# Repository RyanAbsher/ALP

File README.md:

# ALP

A wireless control system for a balloon-based aerial cave photography lighting platform.

## Introduction
A friend of mine has for a long time wanted to photograph the top of a particular cave chamber that has never been photographed before. The chamber is 396 feet tall, so access to the top is obviously somewhat limited. In the past they have used a 6' diameter weather balloon to lift lighting to the top, then used telephoto lenses to photograph it from the ground. This time they are putting the cameras on the balloon, but they didn't have a good way to control the equipment from the ground. This project is the solution to that problem.

## Hardware
The board is based on an STM32 microcontroller. There are three different boards needed for this project: 1 on the ballon, and 2 in control boxes on the ground. I have designed this PCB so that the same design can be used for all of the locations. It is also generic enough that it can be adapted if this particular project changes, or if we want to use it for other projects in the future. There are 8 dedicated relay outputs (5A DC Max) and 16 general IO connectors. These can be used as inputs or outputs, and each bank of 4 connectors has a jumper that can be used to select either 5v or 3.3v outputs. Each of these 16 outputs can also optionally be used as a servo output, with a dedicated servo driver IC on-board.

Communication between boards is accomplished using USART. The two control boxes are connected with a cable. The balloon-mounted board uses HC-12 serial radio modules to communicate with the primary control box on the ground. In ground-based tests of these radios we have achieved effective communication over distances greater than 1400 meters. I do not anticipate any problem using them to communicated over ~120 meters.

Users on the ground can use the two control boxes to control various equipment on the balloon. There is a DSLR camera mounted on the balloon, and the ISO, Aperture, and Shutter speed can be set from the ground. The shutter can of course also be triggered from the ground. The DSLR is mounted on a custom pan/tilt servo gimbal, and this is fully controllable from the ground.

There are 3 powerful LED lights mounted on the balloon, these are controlled through some of the relay outputs, and their direction can be controlled with a servo attached to each.

There are various other pieces of hardware that are controllable from the ground, although the configuration and type of such is likely to change as the project continues.

## Prototype

The photo above contains the laser-etched acrylic control panels, and the stripboard working prototype that I built. While it admittedly doesn't look that great, it did serve it's purpose in that it showed all of the pieces of the system could communicate and function as expected.

## To Do
I have an STM32 dev board on the way that has the same chip that I will be using on this board (STM32F103RBT6). I will use it to confirm that it can do everything I expect of it, then I will be ordering the PCBs. I will likely be ordering them from JLCPCB, and will have them assemble the SMT components on at least a few of the boards. The boards will be populated differently depending on which location they are currently in. For example, the control boxes will not need the relays populated. I will hand-solder the relays and connectors as needed.

Once I have the boards in hand, then I can write the necessary software. I programmed the protoype using the Arduino environment, and I was happy with the way the software worked. Since I have the software mostly completed, it should be fairly simple to port it over to the STM32, likely using STs STM32CubeIDE software. When the software is complete, I will add it to this repository.

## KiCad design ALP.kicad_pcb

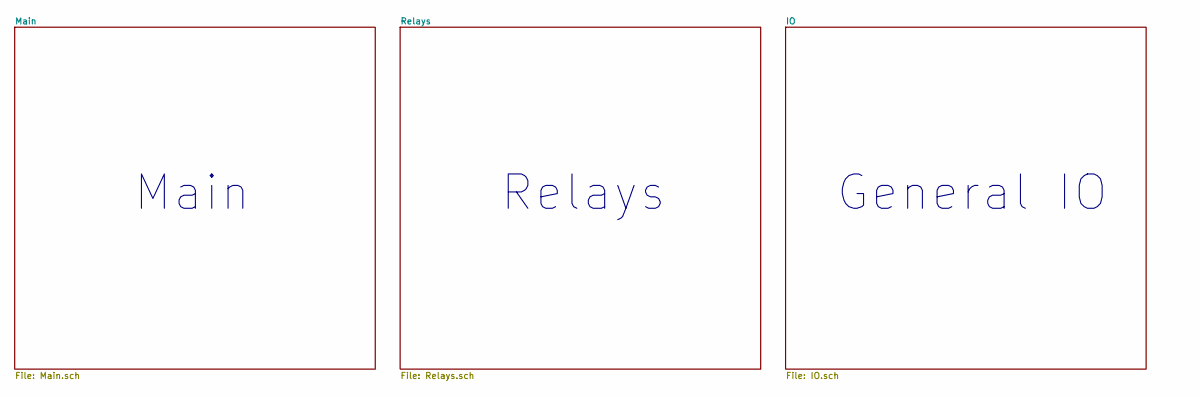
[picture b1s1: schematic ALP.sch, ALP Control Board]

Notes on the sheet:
General IO
Main
Relays

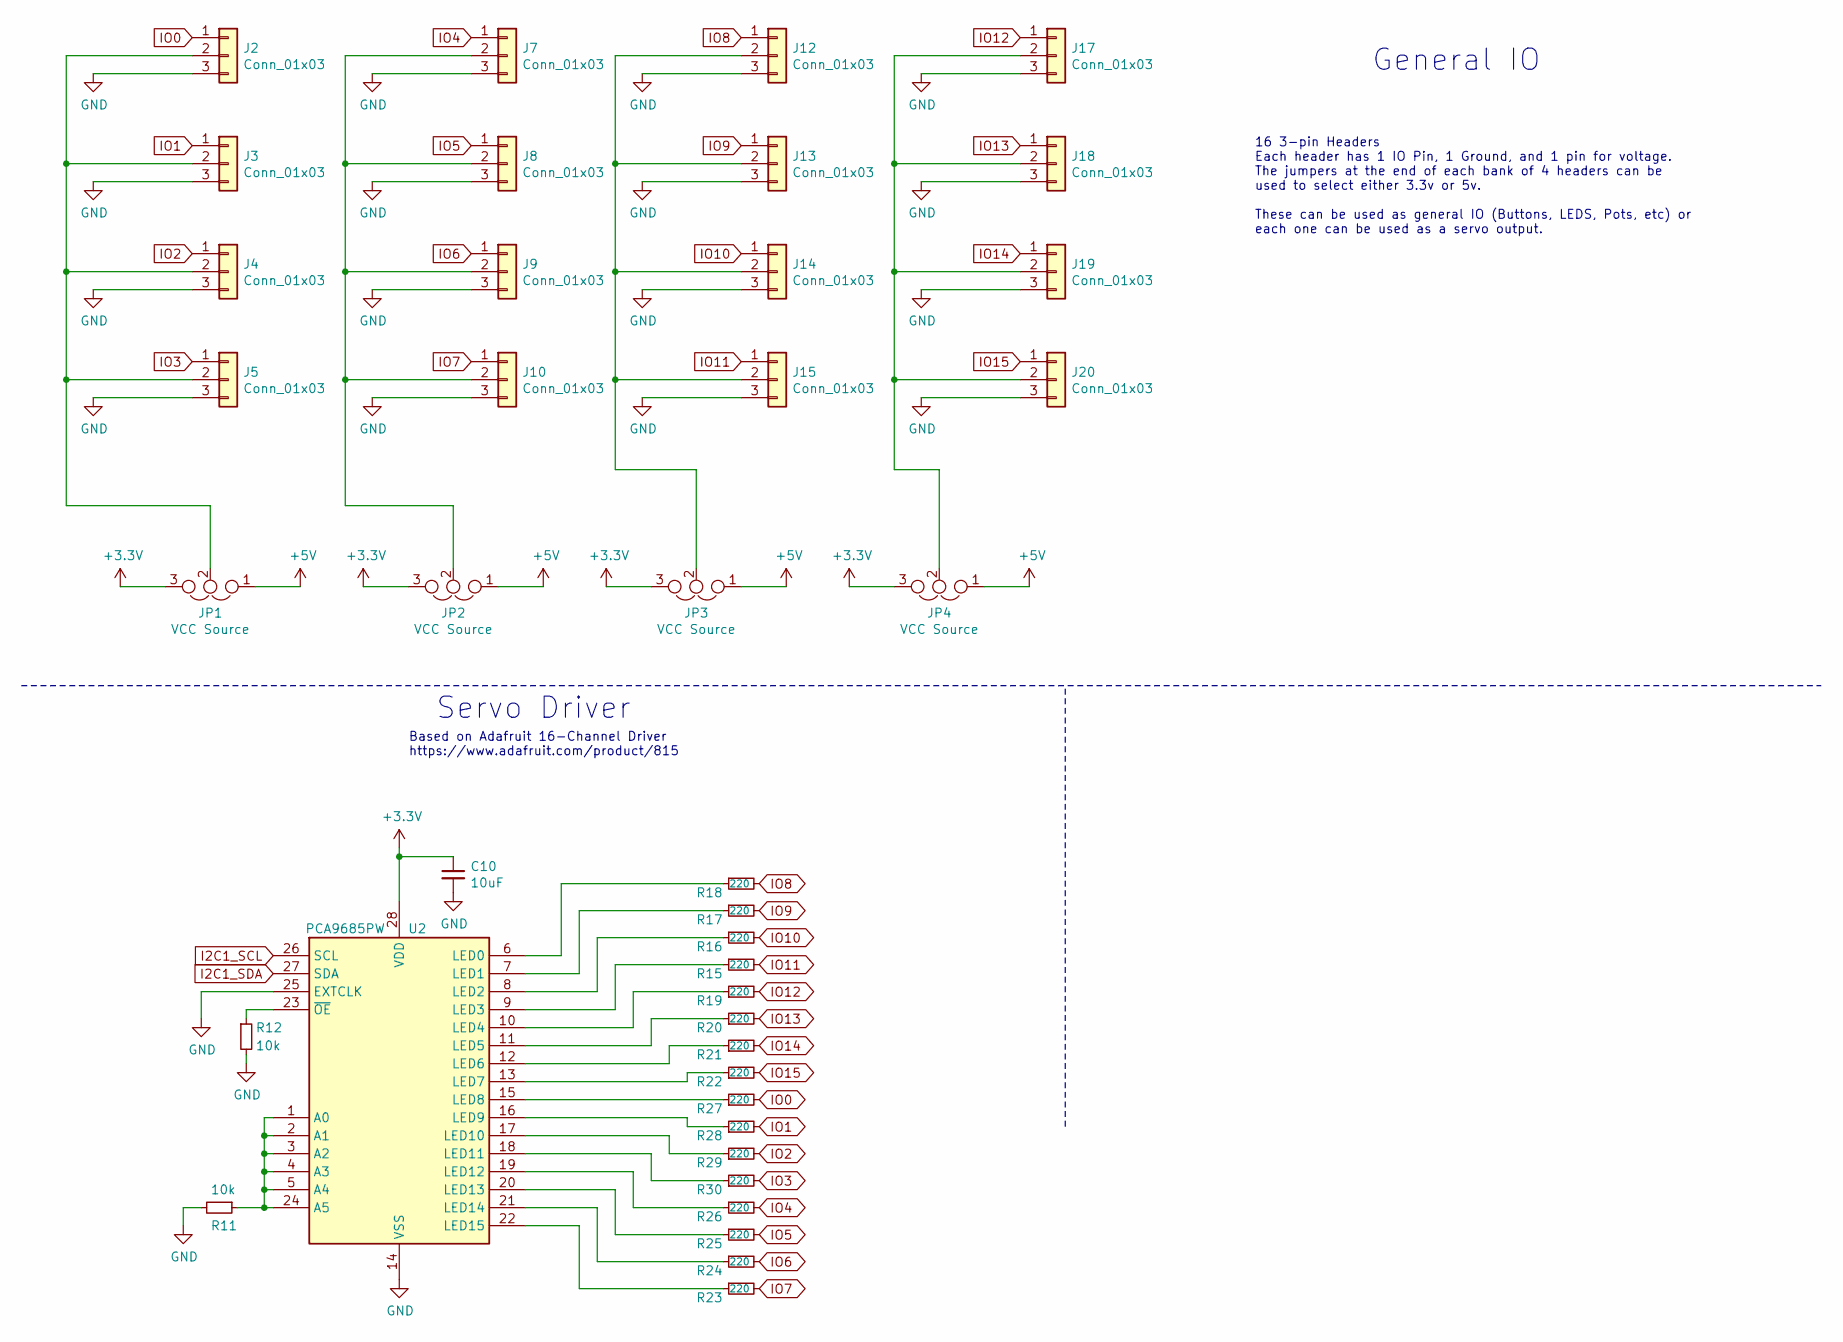
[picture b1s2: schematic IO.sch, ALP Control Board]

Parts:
C10: 10uF; C_0402_1005Metric
J2, J3, J4, J5, J7, J8, J9, J10, J12, J13, J14, J15, J17, J18, J19, J20: Conn_01x03; Molex_PicoBlade_53047-0610_1x03_P1.25mm_Vertical
JP1, JP2, JP3, JP4: VCC Source; PinHeader_1x03_P2.54mm_Vertical
R11, R12: 10k; R_0402_1005Metric
R15, R16, R17, R18, R19, R20, R21, R22, R23, R24, R25, R26, R27, R28, R29, R30: 220; R_0402_1005Metric
U2: PCA9685PW; TSSOP-28_4.4x9.7mm_P0.65mm

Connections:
+3V3: C10.1, JP1.3, JP2.3, JP3.3, JP4.3, U2.28 (VDD); also elsewhere on the board
+5V: JP1.1, JP2.1, JP3.1, JP4.1; also elsewhere on the board
GND: C10.2, J2.3, J3.3, J4.3, J5.3, J7.3, J8.3, J9.3, J10.3, J12.3, J13.3, J14.3, J15.3, J17.3, J18.3, J19.3, J20.3, R11.2, R12.2, U2.14 (VSS), U2.25 (EXTCLK); also elsewhere on the board
I2C1_SCL: U2.26 (SCL); also elsewhere on the board
I2C1_SDA: U2.27 (SDA); also elsewhere on the board
IO0: J2.1, R27.2; also elsewhere on the board
IO1: J3.1, R28.2; also elsewhere on the board
IO2: J4.1, R29.2; also elsewhere on the board
IO3: J5.1, R30.2; also elsewhere on the board
IO4: J7.1, R26.2; also elsewhere on the board
IO5: J8.1, R25.2; also elsewhere on the board
IO6: J9.1, R24.2; also elsewhere on the board
IO7: J10.1, R23.2; also elsewhere on the board
IO8: J12.1, R18.2; also elsewhere on the board
IO9: J13.1, R17.2; also elsewhere on the board
IO10: J14.1, R16.2; also elsewhere on the board
IO11: J15.1, R15.2; also elsewhere on the board
IO12: J17.1, R19.2; also elsewhere on the board
IO13: J18.1, R20.2; also elsewhere on the board
IO14: J19.1, R21.2; also elsewhere on the board
IO15: J20.1, R22.2; also elsewhere on the board
unnamed: J2.2, J3.2, J4.2, J5.2, JP1.2
unnamed: J7.2, J8.2, J9.2, J10.2, JP2.2
unnamed: J12.2, J13.2, J14.2, J15.2, JP3.2
unnamed: J17.2, J18.2, J19.2, J20.2, JP4.2
unnamed: R11.1, U2.1 (A0), U2.2 (A1), U2.3 (A2), U2.4 (A3), U2.5 (A4), U2.24 (A5)
unnamed: R12.1, U2.23 (~OE)
unnamed: R15.1, U2.9 (LED3)
unnamed: R16.1, U2.8 (LED2)
unnamed: R17.1, U2.7 (LED1)
unnamed: R18.1, U2.6 (LED0)
unnamed: R19.1, U2.10 (LED4)
unnamed: R20.1, U2.11 (LED5)
unnamed: R21.1, U2.12 (LED6)
unnamed: R22.1, U2.13 (LED7)
unnamed: R23.1, U2.22 (LED15)
unnamed: R24.1, U2.21 (LED14)
unnamed: R25.1, U2.20 (LED13)
unnamed: R26.1, U2.19 (LED12)
unnamed: R27.1, U2.15 (LED8)
unnamed: R28.1, U2.16 (LED9)
unnamed: R29.1, U2.17 (LED10)
unnamed: R30.1, U2.18 (LED11)

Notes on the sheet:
Servo Driver
Based on Adafruit 16-Channel Driver https://www.adafruit.com/product/815
16 3-pin Headers Each header has 1 IO Pin, 1 Ground, and 1 pin for voltage. The jumpers at the end of each bank of 4 headers can be used to select either 3.3v or 5v. These can be used as general IO (Buttons, LEDS, Pots, etc) or each one can be used as a servo output.
General IO

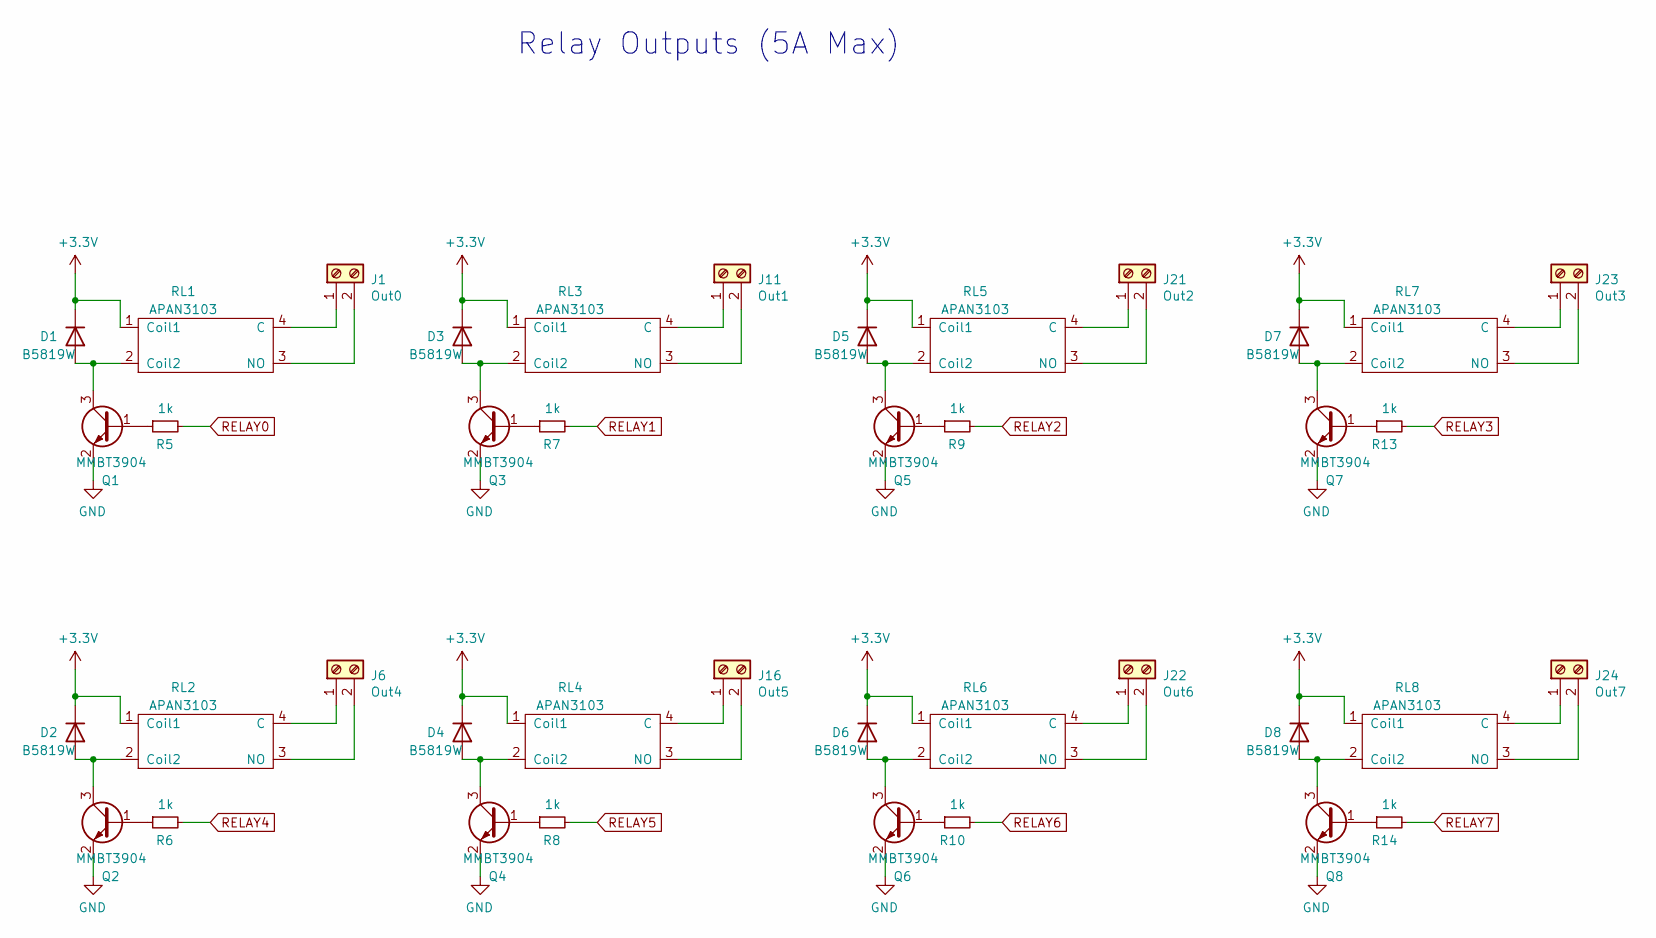
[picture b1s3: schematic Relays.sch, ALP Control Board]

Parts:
D1, D2, D3, D4, D5, D6, D7, D8: B5819W; D_SOD-123; LCSC PN C81598
J1: Out0; CUI_TBL005A-500-02GY-2WT
J6: Out4; CUI_TBL005A-500-02GY-2WT
J11: Out1; CUI_TBL005A-500-02GY-2WT
J16: Out5; CUI_TBL005A-500-02GY-2WT
J21: Out2; CUI_TBL005A-500-02GY-2WT
J22: Out6; CUI_TBL005A-500-02GY-2WT
J23: Out3; CUI_TBL005A-500-02GY-2WT
J24: Out7; CUI_TBL005A-500-02GY-2WT
Q1, Q2, Q3, Q4, Q5, Q6, Q7, Q8: MMBT3904; SOT-23; LCSC Part # C20526
R5, R6, R7, R8, R9, R10, R13, R14: 1k; R_0402_1005Metric; LCSC Part # C11702
RL1, RL2, RL3, RL4, RL5, RL6, RL7, RL8: APAN3103; APAN1303

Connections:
+3V3: D1.1 (K), D2.1 (K), D3.1 (K), D4.1 (K), D5.1 (K), D6.1 (K), D7.1 (K), D8.1 (K), RL1.1 (Coil1), RL2.1 (Coil1), RL3.1 (Coil1), RL4.1 (Coil1), RL5.1 (Coil1), RL6.1 (Coil1), RL7.1 (Coil1), RL8.1 (Coil1); also elsewhere on the board
GND: Q1.2 (E), Q2.2 (E), Q3.2 (E), Q4.2 (E), Q5.2 (E), Q6.2 (E), Q7.2 (E), Q8.2 (E); also elsewhere on the board
unnamed: D1.2 (A), Q1.3 (C), RL1.2 (Coil2)
unnamed: D2.2 (A), Q2.3 (C), RL2.2 (Coil2)
unnamed: D3.2 (A), Q3.3 (C), RL3.2 (Coil2)
unnamed: D4.2 (A), Q4.3 (C), RL4.2 (Coil2)
unnamed: D5.2 (A), Q5.3 (C), RL5.2 (Coil2)
unnamed: D6.2 (A), Q6.3 (C), RL6.2 (Coil2)
unnamed: D7.2 (A), Q7.3 (C), RL7.2 (Coil2)
unnamed: D8.2 (A), Q8.3 (C), RL8.2 (Coil2)
unnamed: J1.1, RL1.4 (C)
unnamed: J1.2, RL1.3 (NO)
unnamed: J6.1, RL2.4 (C)
unnamed: J6.2, RL2.3 (NO)
unnamed: J11.1, RL3.4 (C)
unnamed: J11.2, RL3.3 (NO)
unnamed: J16.1, RL4.4 (C)
unnamed: J16.2, RL4.3 (NO)
unnamed: J21.1, RL5.4 (C)
unnamed: J21.2, RL5.3 (NO)
unnamed: J22.1, RL6.4 (C)
unnamed: J22.2, RL6.3 (NO)
unnamed: J23.1, RL7.4 (C)
unnamed: J23.2, RL7.3 (NO)
unnamed: J24.1, RL8.4 (C)
unnamed: J24.2, RL8.3 (NO)
unnamed: Q1.1 (B), R5.1
unnamed: Q2.1 (B), R6.1
unnamed: Q3.1 (B), R7.1
unnamed: Q4.1 (B), R8.1
unnamed: Q5.1 (B), R9.1
unnamed: Q6.1 (B), R10.1
unnamed: Q7.1 (B), R13.1
unnamed: Q8.1 (B), R14.1
RELAY0: R5.2; also elsewhere on the board
RELAY1: R7.2; also elsewhere on the board
RELAY2: R9.2; also elsewhere on the board
RELAY3: R13.2; also elsewhere on the board
RELAY4: R6.2; also elsewhere on the board
RELAY5: R8.2; also elsewhere on the board
RELAY6: R10.2; also elsewhere on the board
RELAY7: R14.2; also elsewhere on the board

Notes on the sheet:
Relay Outputs (5A Max)

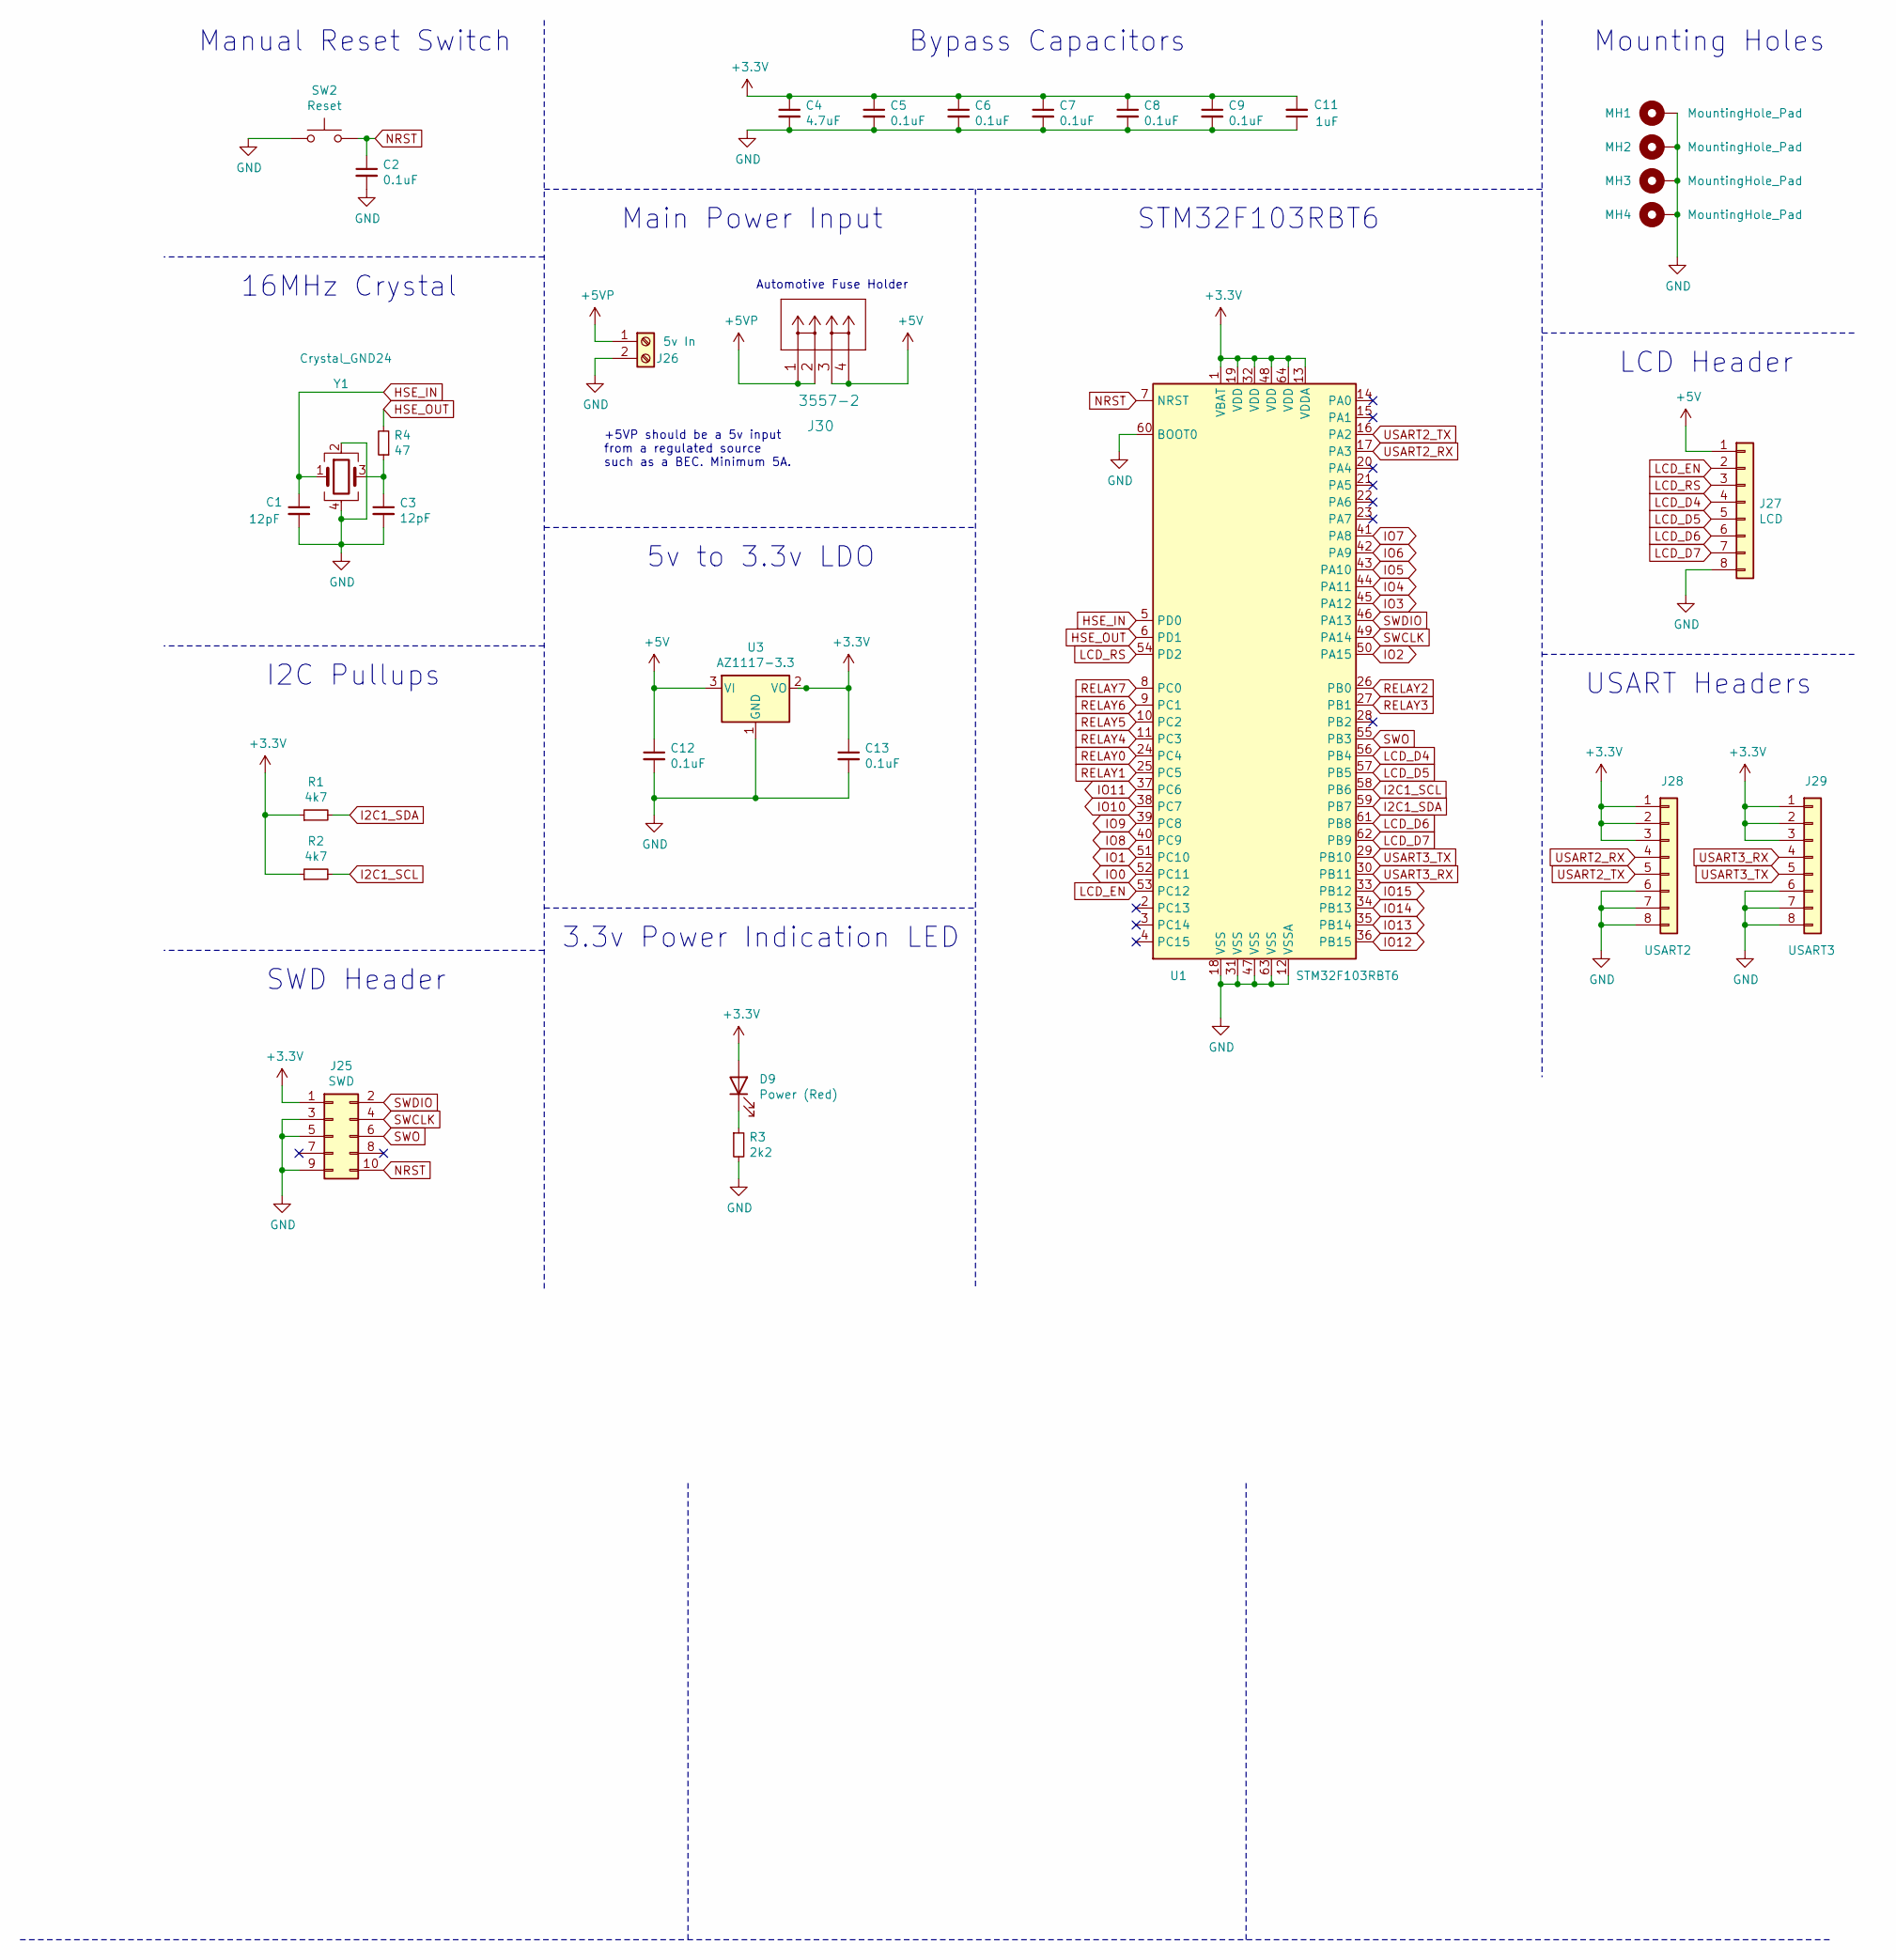
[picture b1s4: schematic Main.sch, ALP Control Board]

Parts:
C1, C3: 12pF; C_0402_1005Metric; LCSC Part # C1547
C2, C5, C6, C7, C8, C9, C12, C13: 0.1uF; C_0402_1005Metric; LCSC Part # C1525
C4: 4.7uF; C_0402_1005Metric; LCSC Part # C23733
C11: 1uF; C_0402_1005Metric; LCSC Part # C52923
D9: Power (Red); LED_0603_1608Metric; LCSC Part # C2286
J25: SWD; PinHeader_2x05_P1.27mm_Vertical
J26: 5v In; CUI_TBL005A-500-02GY-2WT
J27: LCD; Molex_PicoBlade_53047-0810_1x08_P1.25mm_Vertical
J28: USART2; Molex_PicoBlade_53047-0810_1x08_P1.25mm_Vertical
J29: USART3; Molex_PicoBlade_53047-0810_1x08_P1.25mm_Vertical
J30: 3557-2
MH1, MH2, MH3, MH4: MountingHole_Pad; MountingHole_3mm_Pad_Via
R1, R2: 4k7; R_0402_1005Metric; LCSC Part # C25900
R3: 2k2; R_0402_1005Metric; LCSC Part # C25879
R4: 47; R_0402_1005Metric; LCSC Part # C25118
SW2: Reset; SW_SPST_PTS645
U1: STM32F103RBT6; LQFP-64_10x10mm_P0.5mm; LCSC Part # C8735
U3: AZ1117-3.3; SOT-223-3_TabPin2; LCSC Part # C6186
Y1: Crystal_GND24; Crystal_SMD_3225-4Pin_3.2x2.5mm; LCSC Part # C13738

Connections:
+3V3: C4.1, C5.1, C6.1, C7.1, C8.1, C9.1, C11.2, C13.1, D9.2 (A), J25.1, J28.1, J28.2, J28.3, J29.1, J29.2, J29.3, R1.1, R2.1, U1.1 (VBAT), U1.13 (VDDA), U1.19 (VDD), U1.32 (VDD), U1.48 (VDD), U1.64 (VDD), U3.2 (VO); also elsewhere on the board
+5V: C12.1, J27.1, J30.3, J30.4, U3.3 (VI); also elsewhere on the board
+5VP: J26.1, J30.1, J30.2
GND: C1.2, C2.2, C3.2, C4.2, C5.2, C6.2, C7.2, C8.2, C9.2, C11.1, C12.2, C13.2, J25.3, J25.5, J25.9, J26.2, J27.8, J28.6, J28.7, J28.8, J29.6, J29.7, J29.8, MH1.1, MH2.1, MH3.1, MH4.1, R3.2, SW2.1, U1.12 (VSSA), U1.18 (VSS), U1.31 (VSS), U1.47 (VSS), U1.60 (BOOT0), U1.63 (VSS), U3.1 (GND), Y1.2, Y1.4; also elsewhere on the board
HSE_IN: C1.1, U1.5 (PD0), Y1.1
HSE_OUT: R4.2, U1.6 (PD1)
I2C1_SCL: R2.2, U1.58 (PB6); also elsewhere on the board
I2C1_SDA: R1.2, U1.59 (PB7); also elsewhere on the board
IO0: U1.52 (PC11); also elsewhere on the board
IO1: U1.51 (PC10); also elsewhere on the board
IO2: U1.50 (PA15); also elsewhere on the board
IO3: U1.45 (PA12); also elsewhere on the board
IO4: U1.44 (PA11); also elsewhere on the board
IO5: U1.43 (PA10); also elsewhere on the board
IO6: U1.42 (PA9); also elsewhere on the board
IO7: U1.41 (PA8); also elsewhere on the board
IO8: U1.40 (PC9); also elsewhere on the board
IO9: U1.39 (PC8); also elsewhere on the board
IO10: U1.38 (PC7); also elsewhere on the board
IO11: U1.37 (PC6); also elsewhere on the board
IO12: U1.36 (PB15); also elsewhere on the board
IO13: U1.35 (PB14); also elsewhere on the board
IO14: U1.34 (PB13); also elsewhere on the board
IO15: U1.33 (PB12); also elsewhere on the board
LCD_D4: J27.4, U1.56 (PB4)
LCD_D5: J27.5, U1.57 (PB5)
LCD_D6: J27.6, U1.61 (PB8)
LCD_D7: J27.7, U1.62 (PB9)
LCD_EN: J27.2, U1.53 (PC12)
LCD_RS: J27.3, U1.54 (PD2)
NRST: C2.1, J25.10, SW2.2, U1.7 (NRST)
unnamed: C3.1, R4.1, Y1.3
unnamed: D9.1 (K), R3.1
RELAY0: U1.24 (PC4); also elsewhere on the board
RELAY1: U1.25 (PC5); also elsewhere on the board
RELAY2: U1.26 (PB0); also elsewhere on the board
RELAY3: U1.27 (PB1); also elsewhere on the board
RELAY4: U1.11 (PC3); also elsewhere on the board
RELAY5: U1.10 (PC2); also elsewhere on the board
RELAY6: U1.9 (PC1); also elsewhere on the board
RELAY7: U1.8 (PC0); also elsewhere on the board
SWCLK: J25.4, U1.49 (PA14)
SWDIO: J25.2, U1.46 (PA13)
SWO: J25.6, U1.55 (PB3)
USART2_RX: J28.4, U1.17 (PA3)
USART2_TX: J28.5, U1.16 (PA2)
USART3_RX: J29.4, U1.30 (PB11)
USART3_TX: J29.5, U1.29 (PB10)

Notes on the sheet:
Manual Reset Switch
16MHz Crystal
SWD Header
I2C Pullups
Mounting Holes
LCD Header
USART Headers
Bypass Capacitors
5v to 3.3v LDO
Automotive Fuse Holder
Main Power Input
3.3v Power Indication LED
+5VP should be a 5v input from a regulated source such as a BEC. Minimum 5A.
STM32F103RBT6

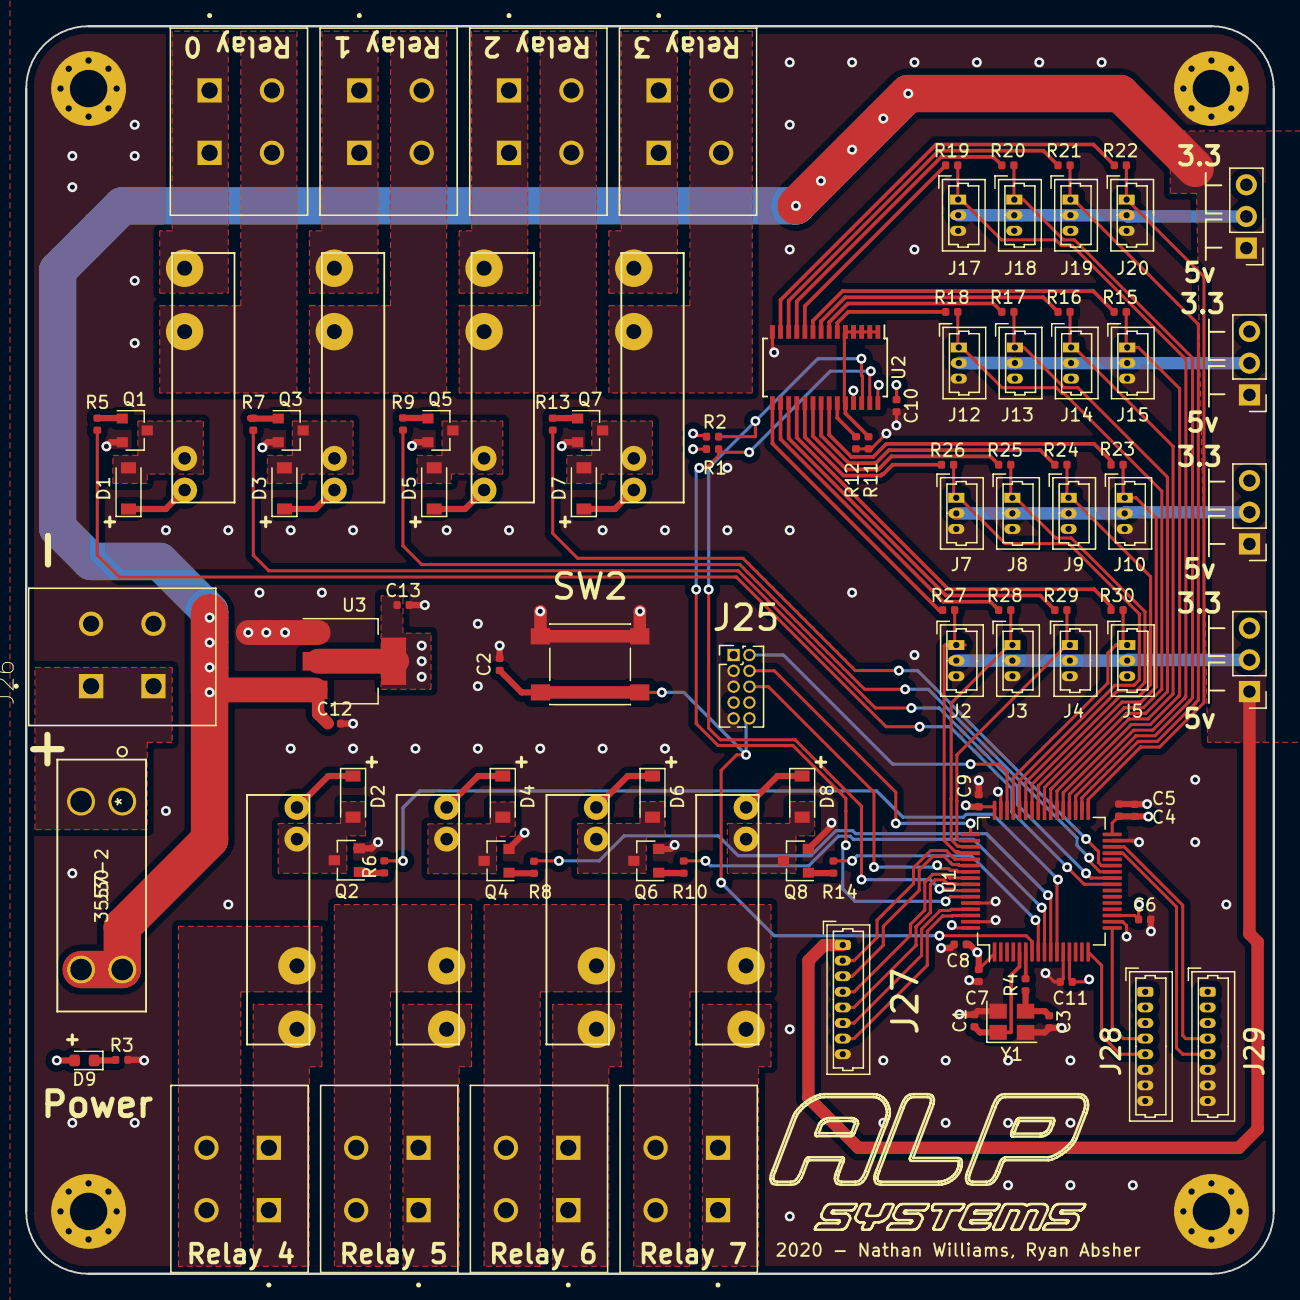
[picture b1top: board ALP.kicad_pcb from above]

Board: 4 copper layers, 100.0 x 100.0 mm, 111 parts (0 on the bottom side), 102 nets.

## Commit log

2020-10-16 Added Photo of Prototype

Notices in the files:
parts and their libraries:
Copyright 2016 Accelerated Designs. All rights reserved.
